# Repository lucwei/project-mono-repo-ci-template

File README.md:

# Project Name

<!-- TODO: one-paragraph description of the project -->

## Firmware Status

## PCB Renders

<!-- PCB_RENDERS_START -->

## pcb_1

| 2D Top | 2D Bottom |
|--------|----------|
|  |  |

| 3D Top | 3D Bottom |
|--------|----------|
|  |  |

[Browse all outputs](https://lucwei.github.io/project-mono-repo-ci-template/hardware/pcb_1/documentation/web/pcb_1-navigate.html)

<!-- PCB_RENDERS_END -->

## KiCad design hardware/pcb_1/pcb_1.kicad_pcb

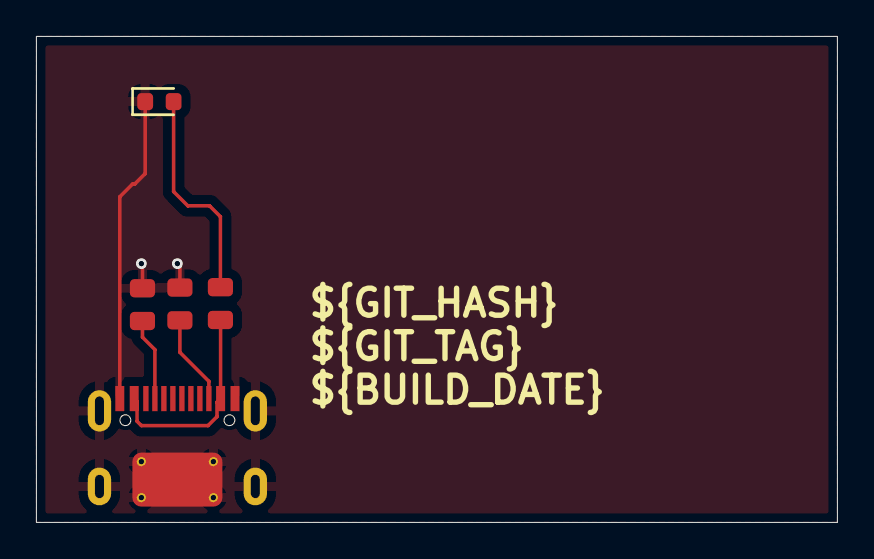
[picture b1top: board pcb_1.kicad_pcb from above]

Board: 2 copper layers, 44.5 x 27.0 mm, 5 parts (0 on the bottom side), 5 nets.

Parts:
D1: Red; D_0603
J1: Connector, USB-TYPE-C-16P; TYPE-C-SMD_HX-TYPE-C-16PIN
R1: 1kΩ; R_0805
R2, R3: 5.1kΩ; R_0805

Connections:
GND: D1.1, J1.A12B1 (GND), J1.B12A1 (GND), J1.S1 (SHIELD), R2.2, R3.2
unnamed: D1.2, R1.2
unnamed: J1.A5 (CC1), R3.1
unnamed: J1.B5 (CC2), R2.1
VBUS: J1.A9B4 (VBUS), J1.B9A4 (VBUS), R1.1

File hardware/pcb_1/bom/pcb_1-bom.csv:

References,Quantity Per PCB,Value,Footprint,MPN,Description
D1,1,Red,D_0603,,-40°C~+85°C Red 0603 LED Indication - Discrete ROHS
J1,1,"Connector, USB-TYPE-C-16P",TYPE-C-SMD_HX-TYPE-C-16PIN,,3A 1 Horizontal attachment 16P Female -25℃~+85℃ Type-C SMD USB Connectors ROHS
R1,1,1kΩ,R_0805,,125mW Thick Film Resistors 150V ±100ppm/°C ±1% 1kΩ 0805 Chip Resistor - Surface Mount ROHS
R2 R3,2,5.1kΩ,R_0805,,125mW Thick Film Resistors 150V ±100ppm/°C ±1% 5.1kΩ 0805 Chip Resistor - Surface Mount ROHS





Project info:
Schematic:,pcb_1
Variant:,default
Revision:,
Date:,2026-04-03_13-13-15
KiCad Version:,9.0.7+1
Statistics:
Component Groups:,4
Component Count:,5
Fitted Components:,5
Number of PCBs:,1
Total Components:,5

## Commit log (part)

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2026-03-28 points pass/fail badges to main branch
2026-03-28 points fabrication badgeto main branch
2026-03-29 add kicad drawing sheet template
2026-03-29 add manual trigger for fabrication workflow
2026-03-29 ci: update all renders and schematics [skip ci]
2026-03-29 fix badges pass/fail url
2026-03-29 add auto_crop and transparent background for PCB 3D renderings
2026-03-29 add automatic iBom generation
2026-03-29 ci: update renders, schematics, and iBOM [skip ci]
2026-03-30 test change
2026-03-30 ci: add matrix discovery to ERC/DRC and gate fabrication on checks
2026-03-30 test-workflow
2026-03-30 fix: remove invalid erc/drc output types from kibot config
2026-03-30 test-workflow2
2026-03-30 chore: configure erc/drc to ignore warnings
2026-03-30 test/workflow-validation
2026-03-30 fix: erc and drc preflight options
2026-03-30 change needs conditon for fabrication job
2026-03-30 Revert "chore: configure erc/drc to ignore warnings"
    This reverts commit 47dfe07855b239ed040246ee675204eae81ccf0f.
2026-03-30 Revert "test/workflow-validation"
    This reverts commit f41bfac697a76066e7a57eaa081d6dce11ab9e38.
2026-03-30 Revert "fix: remove invalid erc/drc output types from kibot config"
    This reverts commit 96a04a1763ee72710dfb93b1c4664f3ef5f8c9d6.
2026-03-30 Revert "change needs conditon for fabrication job"
    This reverts commit 5bcdf67d4ae353831819afe9a70c06b539e3c42d.
2026-03-30 Revert "fix: erc and drc preflight options"
    This reverts commit f8500a87e54cc20fdd0b1399fb45c233e5567cd0.
2026-03-30 Revert "test-workflow2"
    This reverts commit 1962c5f5c92d15f8528ae997ccc27628ec9eed0e.
2026-03-30 Revert "test-workflow"
    This reverts commit 1e65093ea42dd0d6fb7e03bbed3175e72afe33ec.
2026-03-30 Revert "ci: add matrix discovery to ERC/DRC and gate fabrication on checks"
    This reverts commit 8d5c5fa814520af7530ff5c17717a19c8ef7b59a.
2026-03-30 Revert "ci: update renders, schematics, and iBOM [skip ci]"
    This reverts commit e24bef53439373788bb2a251f4070d2847a48f6e.
2026-03-30 Revert "test change"
    This reverts commit c6a32f49c12a29cbde64a1e56dcd0d5c82cf73ba.
2026-03-30 testing
2026-03-30 add needs ERC DRC
